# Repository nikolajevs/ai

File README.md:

# GrowBox — контроллер гроубокса

Прошивка ESP32 и собственная плата управления освещением, вентиляцией, поливом и обогревом. Температура и влажность измеряются внешним SHT4x; настройки доступны через веб-интерфейс, расписания используют RTC, журнал сохраняется на microSD.

## Структура репозитория

| Папка | Содержимое |
| --- | --- |
| [softwareEU/](softwareEU/README.md) | Прошивка PCB_EU для ESP32-WROOM-32E-N4, веб-интерфейс и инструкция по сборке |
| [hardware/](hardware/README.md) | Проекты KiCad 10, BOM, модели деталей, корпус и файлы изготовления |
| [parts-catalog/](parts-catalog/README.md) | Локальный каталог цен и остатков четырёх магазинов: поиск, проверка BOM PCB_EU, подбор аналогов |
| [tests/](tests/) | Автоматические тесты веб-интерфейса |
| [vps-docs/](vps-docs/README.md) | Состояние VPS после удаления KiCad и обслуживание прочих сервисов |

## Аппаратная часть

- [PCB_EU](hardware/PCB_EU/README.md) — текущая плата: ESP32-WROOM-32E-N4, вход 24 В, четыре слоя, 100×100 мм, детали только из магазинов ЕС. Прошивка — [softwareEU/](softwareEU/README.md).
- [PCB_V1](hardware/PCB_V1/README.md) — предыдущий проект платы, отдельный от PCB_EU. Прошивка `softwareEU/` его не поддерживает.
- [cheap-version](hardware/cheap-version/README.md) — вариант платы с использованием имеющихся компонентов. Файлы изготовления и состояние проверок описаны в его [FAB.md](hardware/cheap-version/FAB.md).
- [Корпус](hardware/enclosure/README.md) — параметрическая модель для 3D-печати; перед использованием сверяйте её с выбранной версией платы.

## Начало работы

Для прошивки PCB_EU откройте `softwareEU/softwareEU.ino`; зависимости, загрузка веб-интерфейса и проверки описаны в [softwareEU/README.md](softwareEU/README.md).

Для платы PCB_EU откройте `hardware/PCB_EU/PCB_EU.kicad_pro`; распиновка и состояние разработки описаны в [DESIGN.md](hardware/PCB_EU/DESIGN.md).

Правила работы с репозиторием — [AGENTS.md](AGENTS.md).

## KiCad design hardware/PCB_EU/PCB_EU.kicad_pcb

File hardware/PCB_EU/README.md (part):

# GrowBox — новая плата с европейской закупкой

**EU-0.1, состояние на 23.10.2026: все клеммы и разъёмы у краёв платы, радиатор только у LED1 (Q601 без радиатора), вентиляторы на хидерах KF2510-4A, SHT4x на угловом XH2.54-4P-90; все электролиты сверху, снизу детали не выше 8,05 мм; плата разведена полностью (см. «Разводка 21.10.2026» и «Силовой контур LED2 и ключи LED» в [DESIGN.md](DESIGN.md)); силовой контур LED2 проложен вручную, ключи LED — Q501 TK22E10N1 и Q601 CSD19534KCS; добавлен монитор мощности INA226.** Открыть [PCB_EU.kicad_pro](PCB_EU.kicad_pro) в KiCad 10.0.7. Проект содержит схему и [PCB_EU.kicad_pcb](PCB_EU.kicad_pcb): 196 позиций схемы, 113 сверху / 83 снизу, четыре слоя меди; 1451 участок дорожек, 345 переходных, плоскость GND на In1.Cu и заливки GND на F.Cu/B.Cu. Неразведённых соединений нет; физическая сборка и крепление радиатора на купленной детали не подтверждены.

Сохраняются функции PCB_V1: два LED-канала с общей яркостью, два независимых PWM/тахоканала вентиляторов, PTC, помпа, SHT4x, поплавок, RTC с CR2032, microSD, Wi-Fi и существующие функции интерфейса/расписаний. Функциональное основание — `origin/main` `1d6b1eaf1273149b32eb1cf5c91fc69ff6a6ca09`.

**Прошивка PCB_EU находится в [softwareEU/](../../softwareEU/README.md)**: ESP32-WROOM-32E-N4, 4 МБ, RTC MCP7940N и измерение мощности INA226. Команды сборки, тесты и список стендовых проверок приведены в её README; аппаратные испытания предстоят. Прежний бинарник PCB_V1 несовместим: GPIO и RTC отличаются, например прежний GPIO25 помпы теперь управляет LED.

## Файлы

| Файл | Назначение |
|---|---|
| [DESIGN.md](DESIGN.md) | Решения, GPIO, разъёмы, состояния при сбросе и открытые вопросы |
| [BOM_allocated.csv](BOM_allocated.csv) | Закупка с MPN/артикулами, количеством, реальными Ref и ссылками |
| [BOM_allocated.json](BOM_allocated.json) | Тот же состав для автоматической проверки |
| [design.json](design.json) | Полная спецификация выводов, цепей и компонентов |
| [placement.json](placement.json) | Координаты всех 196 позиций, стороны, предварительные резервы и крепление |
| [Размещение сверху](review/PCB_placement_front.png) / [снизу](review/PCB_placement_back.png) | Native KiCad виды PCB с фактической разводкой; снизу зеркально |
| [routing.json](routing.json) / [review/routing.json](review/routing.json) | План силовых соединений LED1 и проверка физической связности меди, включая обе анодные площадки D501; итог разводки и ширины по классам |
| [routing/](routing) | Сессии Freerouting 2.4.1, из которых `tools/route_board.py` воспроизводит разводку |
| [PCB_EU.kicad_dru](PCB_EU.kicad_dru) | Правил DRC нет: прежние сплошные подключения C609 и C510 после переноса электролитов наверх не нужны |
| [footprint_assignments.json](footprint_assignments.json) | Точные механические назначения для 17 MPN, источники и SHA-256 чертежей |
| [procurement_2026-10-20.json](procurement_2026-10-20.json) | Датированный снимок цен/MOQ; не текущая оферта |
| [review/validation.json](review/validation.json) | Версия KiCad, результат проверок, контрольные суммы исходников |
| [review/connectivity.txt](review/connectivity.txt) | 56 проверок соединений и количества покупок |
| [review/footprints.json](review/footprints.json) | Проверки 196 назначений, нумерации площадок, геометрии и загрузки KiCad |
| [review/footprint_drc.json](review/footprint_drc.json) | DRC изолированных библиотечных образцов; не DRC изделия |
| [review/placement.json](review/placement.json) | Сверка PCB/netlist, courtyards, пайка противоположной стороны, RF и механические резервы |
| [review/pcb_drc.json](review/pcb_drc.json) | DRC реального PCB: 0 геометрических / 0 parity / 0 неразведённых |
| [Посадки 1](review/Footprints_mechanical_1.png) / [Посадки 2](review/Footprints_mechanical_2.png) | Отрисовка 12 механических посадок в KiCad, увеличенных отдельно |
| [review/erc.json](review/erc.json) | ERC KiCad; стандартные отключённые категории перечислены в файле |
| [review/netlist.xml](review/netlist.xml) | Netlist, экспортированный самим KiCad |
| [libraries/SOURCES.md](libraries/SOURCES.md) | Источники графики символов и выбранных посадочных мест |

## Закупка

| Поставщик | Детали, НДС включён | Доставка | Сумма |
|---|---:|---:|---:|
| Electrobase | 39,83 € | 2,99 € | 42,82 € |
| Salvats | 35,55 € | 2,88 € | 38,43 € |
| **Всего** | **75,38 €** | **5,87 €** | **81,25 €** |

81 закупочная строка включает минимальные партии, CR2032 и один комплект охлаждения/крепежа/изоляции (после снятия радиатора с Q601 второй комплект убран 23.10.2026). Две строки (KF2510-4A ×2 и XH2.54-4P-90 ×1) добавлены без магазина и цены; DG306 и DG301R куплены по потребности (6 и 1 шт.), запасных нет. Не включены PCB, БП, нагрузки, внешний SHT4x, карта SD, внешняя термозащита PTC, корпус, внешние провода, программатор и инструменты. Заказ не сделан. Ориентир бюджета — около 80 €, жёсткий потолок проверки — 100 €. Разрешённые магазины на 23.10.2026 (список Игоря): Salvats, Electrobase, Semikom, Lemona; в закупке сейчас Electrobase и Salvats. Farnell, Elektrika и Ormix исключены. Нужен БП 24 В не менее 240 Вт / 10 А и внешний термовыключатель PTC.

В схеме пять подтяжек SD CMD/DAT вместо прежней одной: пачек 10k теперь две (+0,11 €). Для трёх затворов AO3422 используются уже оплаченные 1k из пачки вместо отдельных 100R (−0,09 €). Итого изменение к предыдущему подбору: +0,02 €. Фронты PWM вентиляторов с 1k нужно измерить.

21.10.2026 ключи LED IRF540Z (Salvats, 1,70 €) заменены на Toshiba TK22E10N1 (Salvats, 1,38 €, 22 шт. в наличии, цена от 21.10.2026): −0,64 €. Причина — в DESIGN.md, «Ключи LED».

23.10.2026 по решению Игоря заменены три ключа (DESIGN.md, «Ключи LED» и «Q601 без радиатора»). Q601 (LED2): TK22E10N1 → TI CSD19534KCS (Electrobase, 3,09 €, у поставщика 91 шт.; расчётные потери ~0,37 Вт вместо ~0,65 Вт). Q102 и Q703: IRF1010ESPBF → onsemi FDB5800 (Salvats, 2 × 1,98 €, на складе 4 шт.; 6 мОм вместо 12, затвор ±20 В, посадка TO-263-2 та же). TK22E10N1 нужен один (Q501, 1,38 €): второй не покупается. Изменение: IRF 2,42 € → FDB5800 3,96 € (+1,54 €), TK22E10N1 −1,38 €, CSD19534KCS +3,09 €; итого +3,25 €, закупка 82,50 € → 85,75 €. Цены и наличие этих трёх строк проверены 23.10.2026; остальные строки оставлены по снимку 20–21.10.2026, доставка 5,87 € прежняя, посылок по-прежнему две (Electrobase и Salvats).

23.10.2026 по решению Игоря изменены ещё две части закупки. C301/C302 (нагрузка кварца RTC, нужен C0G): Salvats C1206C100J5GAC → KEMET C1206C100J5GACTU у Electrobase (2 × 0,25 € вместо 2 × 0,10 €, у поставщика больше 1000 шт.; карточка Salvats называет Y5V, карточка Electrobase — 10 пФ 50 В C0G ±5 %, TU — суффикс упаковки), +0,30 €. Второй комплект охлаждения убран: RAD-DY-GF/3, TO220-SET и SMICA-TO220-2 по 1 шт. вместо 2 (−1,38 €), после снятия радиатора с Q601 он не нужен. Итого −1,08 €, закупка 85,75 € → 84,67 €; доставка 5,87 € и две посылки прежние. Цена и наличие C1206C100J5GACTU проверены 23.10.2026.

23.10.2026 по решению Игоря («да все 3» на разбор выгрузки цен магазинов от 23.10.2026; сам файл в репозиторий не добавлен) изменены ещё три части закупки. D501/D601: Vishay SS5P10-M3/86A → SS8PH10-M3/86A (Electrobase, 2 × 0,59 € вместо 2 × 1,09 €, у поставщика больше 1000 шт.; тот же корпус TO-277A и та же посадка, 8 А вместо 5 А), −1,00 €. J201: ZL2019-20 (двусторонняя планка на 20 контактов, 0,63 €) → ZL201-10G (Salvats, обычная однорядная планка на 10 контактов, 0,16 €, на складе 41 шт.; режутся 6 контактов, остаются 4), −0,47 €. DG306 покупается 6 шт. вместо 11, DG301R — 1 шт. вместо 2: запасные клеммы не берутся (−1,95 €). Итого −3,42 €, закупка 84,67 € → 81,25 €; доставка 5,87 € и две посылки прежние. Цена и наличие SS8PH10-M3/86A проверены на странице Electrobase 23.10.2026; цена и остаток ZL201-10G взяты из выгрузки, страницы Salvats в тот момент отвечали 429. Сверка посадки и причины — DESIGN.md, «Выходные диоды D501/D601» и «Разъёмы и точные распиновки».

21.10.2026 добавлено измерение мощности платы (DESIGN.md, «Измерение мощности (INA226)»): INA226AIDGSR (Electrobase, 3,94 € за шт.; карточка товара — катушка 2500 шт., наличие и продажа поштучно не подтверждены), шунт из двух 0R01 2512 3 Вт (Salvats, 2 × 0,24 €) и стабилитрон BZV55-C33 (Salvats, 0,13 €). Резистор 1k и конденсатор 100 нФ взяты из уже оплаченных пачек. Итого +4,55 €.

Исправления 21.10.2026: убран TC4427A и его обвязка (−2,53 € и 10 мкФ −0,22 €), добавлена защита от переполюсовки (второй IRF1010ES +1,21 €, 2×5,6k и 10k +0,09 €), R702 заменён на 4,7k 1206 (+0,04 €). C208 1 мкФ взят из уже оплаченной пачки. Итого −1,41 € к прежним 80,00 €.

## Проверки

**Состояние после правок 23.10.2026 (Q601, Q102, Q703, C301/C302, D501/D601 и J201).** Полный `tools/run_checks.py` выполнен 23.10.2026 на KiCad 10.0.7 (версия отчётов) со Shapely 2.0.3 и `pcbnew` из того же пакета: ERC 0, 56 проверок связности, 2198 проверок посадок, 22 991 проверка размещения, DRC со сверкой схемы 0/0/0, разводка полная (1451 дорожка, 345 переходных), скрининг меди 27 сценариев без флагов, JLCPCB 0 FAIL / 3 WARN. Файлы `review/` обновлены этим прогоном, `review/netlist.xml` — экспорт самого KiCad. Поля MPN и Value у D501/D601 и MPN и Design_note у J201 в `PCB_EU.kicad_pcb` исправлены текстом, геометрия платы не менялась. Пересборка платы из исходников (`build_board.py`, `route_power.py`, `route_board.py`, `silkscreen.py`) совпадает с этим `PCB_EU.kicad_pcb`, кроме формата одной строки трёхмерной модели HS1 (правка из PR #86). Физическая примерка, нагрев и поведение преобразователей этими проверками не подтверждены.

Проверено **KiCad CLI 10.0.7**: ERC 0 ошибок/0 предупреждений; 56 проверок, 498 подключённых выводов. Исключений ERC в проекте нет; сохранены четыре стандартные отключённые категории KiCad, перечисленные в `validation.json`.

Для реального PCB: 22 991 проверка размещения; DRC со сверкой схемы — 0 геометрических нарушений, 0 расхождений и **0 неразведённых соединений**. Сборка из `placement.json` и netlist: `build_board.py` + `route_power.py` + `route_board.py` + `silkscreen.py`; результат пересборки описан выше. Отдельно проверены 328 запланированных объектов меди (силовые контуры LED1 и LED2, ручные выводы LM3429, измерение мощности INA226, силовая медь входа, магистрали и питания PTC/LED1 под 1 oz) и 26 физически связанных групп. Проверены обе стороны, нумерация/цепи площадок, THT-маска, courtyards, запас вокруг паек на противоположной стороне, RF и предварительные механические резервы.

Расчётная проверка меди завершена для первого прототипа: добавлены параллельные переходные и путь питания вентиляторов. Наибольший ток переходного 1,55 А в номинале / 1,90 А при изменении сопротивления гильз вдвое; падение +12V до предохранителя вентиляторов около 31 мВ вместо 123 мВ. Подробности, допущения и оставшиеся испытания — DESIGN.md, «Медь и токи»; 27 сценариев — [review/power_copper.json](review/power_copper.json). Выбран и записан в PCB стек JLCPCB JLC04161H-7628: 35 мкм меди снаружи / 15,2 мкм внутри, общая толщина с масками 1,6062 мм. Допуски готовой меди и металлизации нужно подтвердить при расчёте заказа фабрикой.

Радиатор Q501 крепится двумя ножками, запаянными в металлизированные отверстия GND посадки HS1, и винтом М3 к фланцу транзистора через изолирующую прокладку и втулку (решение 22.10.2026, размеры — DESIGN.md, «Радиатор Q501»). Физическая примерка и электрическая изоляция, допустимые токи, нагрев и поведение преобразователей проверяются на прототипе. Визуальный осмотр — за пользователем, производственный ZIP пока не выпускается.

Проверки выполнены на **KiCad 10.0.7**, это целевая версия репозитория. `tools/run_checks.py` проверяет только аппаратную часть PCB_EU; старая PCB_V1 в этот прогон не входит. Прошивка `softwareEU/` собирается и тестируется отдельно по [её инструкции](../../softwareEU/README.md#сборка-и-проверки); работа на реальной плате пока не проверена.

Поле `firmware_build` в [review/validation.json](review/validation.json) говорит, что аппаратные проверки сборку прошивки не выполняют: `softwareEU/` собирается и тестируется отдельно.

Повторить проверки новой схемы с установленным KiCad 10.0.7:

```sh
python3 hardware/PCB_EU/tools/run_checks.py
```

Другую локальную версию разрешать явно, с записью фактической версии в результат:

```sh
python3 hardware/PCB_EU/tools/run_checks.py --kicad-cli /path/to/kicad-cli --allow-other-version
```

Схемы воспроизводятся без сторонних Python-пакетов:

```sh
python3 hardware/PCB_EU/tools/generate.py
```

Специальные посадки воспроизводятся командой `python3 hardware/PCB_EU/tools/generate_footprints.py`. Дополнительный DRC библиотечных образцов: `python3 hardware/PCB_EU/tools/check_footprint_drc.py --kicad-cli /path/to/kicad-cli`; нужен `pcbnew` той же версии в выбранном Python. Этот DRC не проверяет PCB изделия.

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
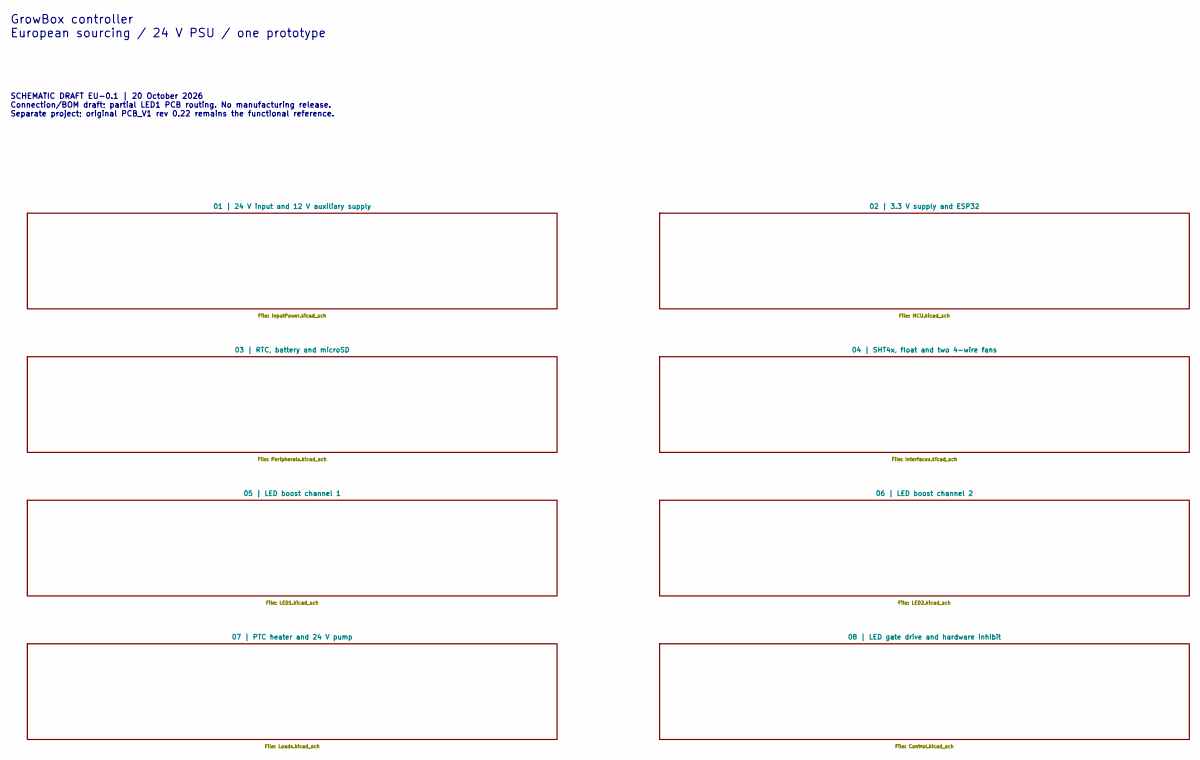
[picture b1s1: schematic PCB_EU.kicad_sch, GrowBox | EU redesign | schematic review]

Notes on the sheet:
GrowBox controller European sourcing / 24 V PSU / one prototype
SCHEMATIC DRAFT EU-0.1 | 20 October 2026 Connection/BOM draft; partial LED1 PCB routing. No manufacturing release. Separate project; original PCB_V1 rev 0.22 remains the functional reference.

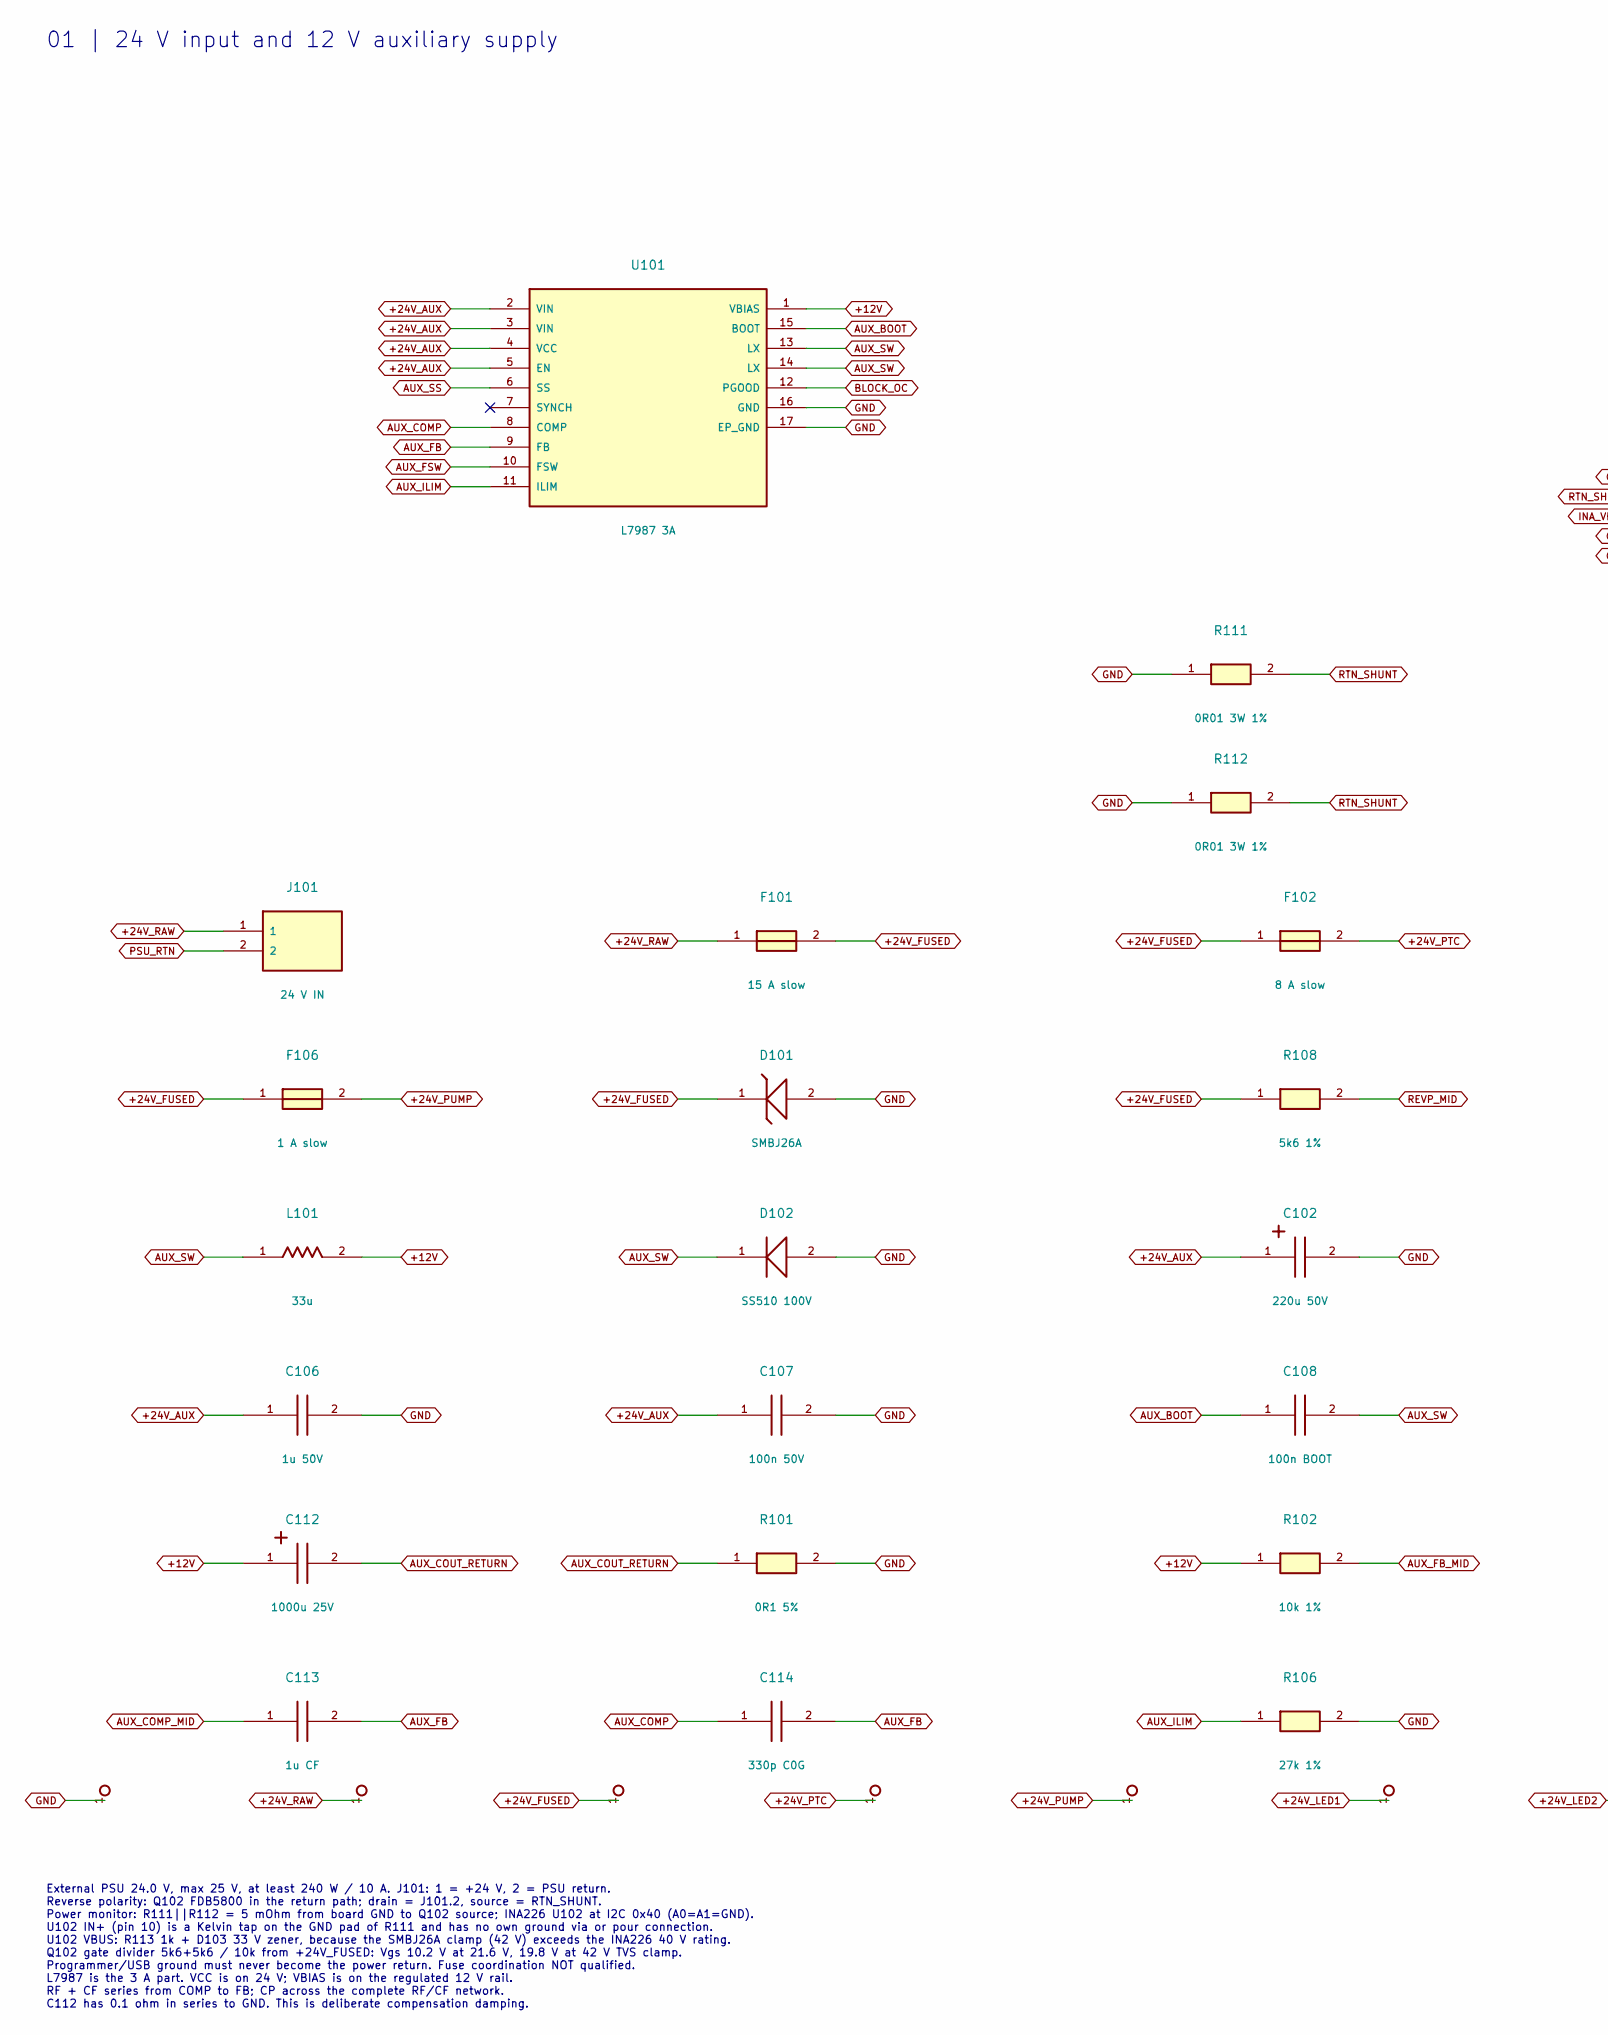
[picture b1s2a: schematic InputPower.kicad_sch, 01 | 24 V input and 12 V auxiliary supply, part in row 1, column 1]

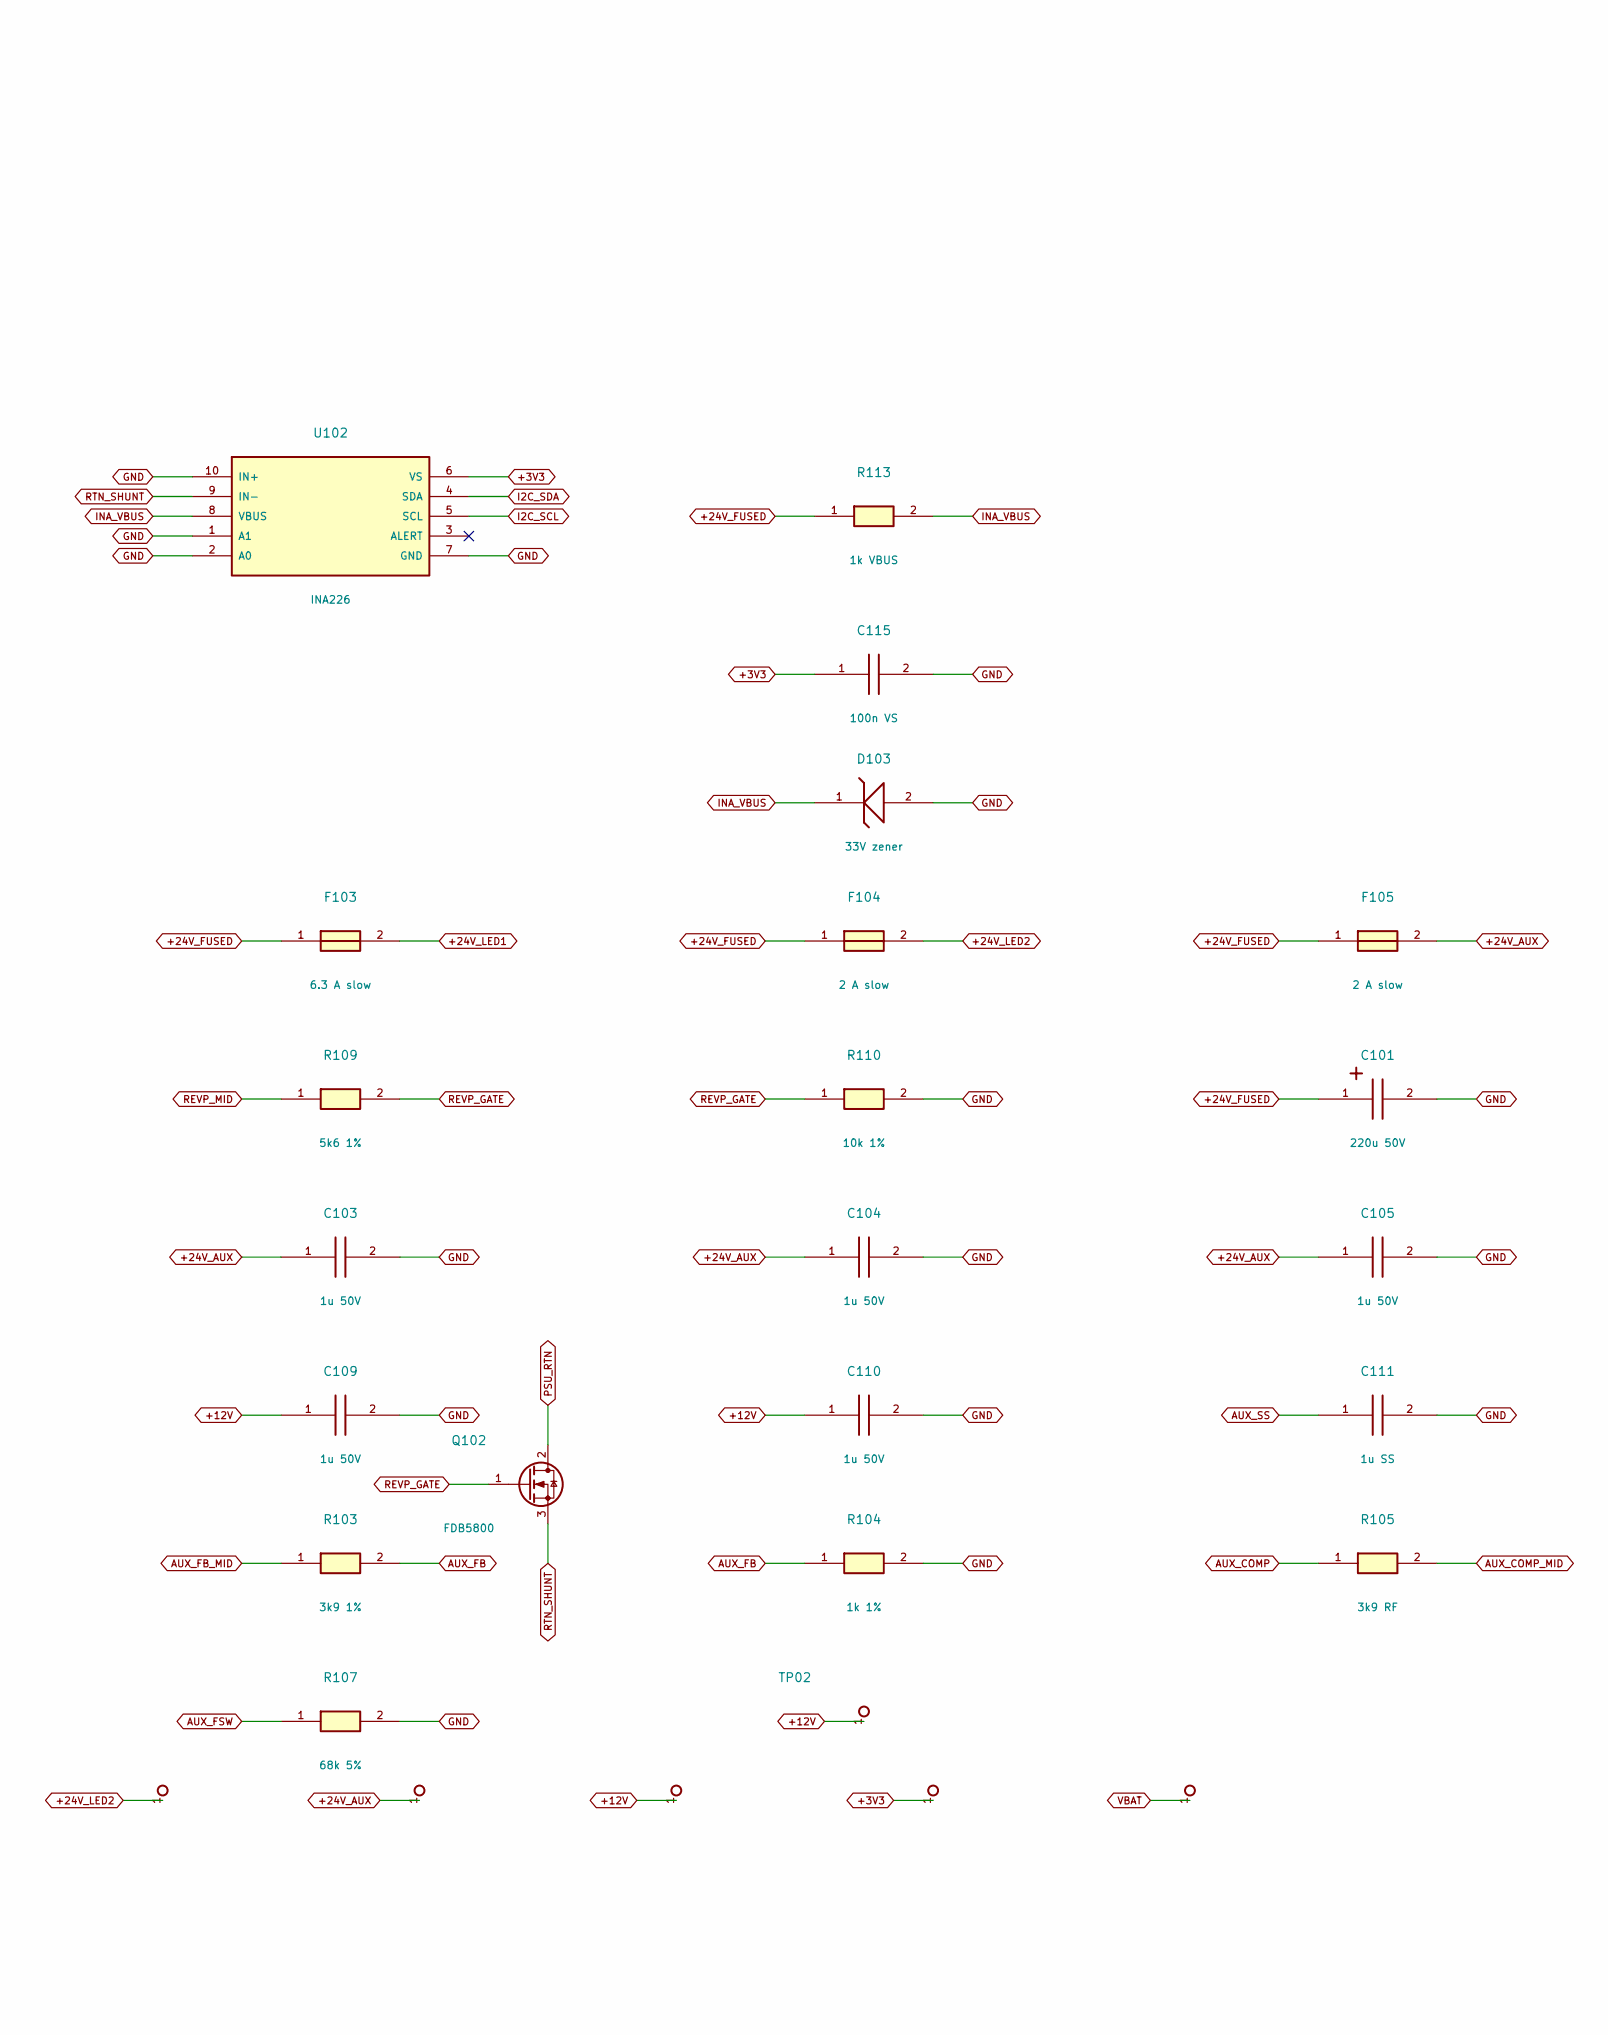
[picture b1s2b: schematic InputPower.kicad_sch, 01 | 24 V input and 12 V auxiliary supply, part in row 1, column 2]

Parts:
C101, C102: 220u 50V; CP_Radial_D10.0mm_P5.00mm; MPN UPW1H221MPD
C103, C104, C105, C106, C109, C110: 1u 50V; C_0805_2012Metric; MPN CL21B105KBFNNNG
C107: 100n 50V; C_0805_2012Metric; MPN CL21B104KBCNNNC
C108: 100n BOOT; C_0805_2012Metric; MPN CL21B104KBCNNNC
C111: 1u SS; C_0805_2012Metric; MPN CL21B105KBFNNNG
C112: 1000u 25V; CP_Radial_D10.0mm_P5.00mm; MPN EEUFR1E102
C113: 1u CF; C_0805_2012Metric; MPN CL21B105KBFNNNG
C114: 330p C0G; C_1206_3216Metric; MPN CC1206JRNPO9331
C115: 100n VS; C_0805_2012Metric; MPN CL21B104KBCNNNC
D101: SMBJ26A; D_SMB; MPN SMBJ26A-E3/52
D102: SS510 100V; D_SMC; MPN SS510-YAN
D103: 33V zener; D_MiniMELF; MPN BZV55-C33
F101: 15 A slow; Fuse_Schurter_UST_USI1206_Reflow; MPN 3413.0330.11
F102: 8 A slow; Fuse_Schurter_UST_USI1206_Reflow; MPN 3413.0327.11
F103: 6.3 A slow; Fuse_Schurter_UST_USI1206_Reflow; MPN 3413.0224.11
F104, F105: 2 A slow; Fuse_Schurter_UMT250; MPN 3403.0169.11
F106: 1 A slow; Fuse_Schurter_UMT250; MPN 3403.0166.11
J101: 24 V IN; TerminalBlock_Degson_DG301R-5.0_1x02; MPN DG301R-5.0-2P12
L101: 33u; L_Jantek_JNRH1207; MPN JNRH1207-330M-A
Q102: FDB5800; TO-263-2; MPN FDB5800
R101: 0R1 5%; R_1206_3216Metric; MPN SMD1206-0R1
R102, R110: 10k 1%; R_1206_3216Metric; MPN SMD1206-10K-1%
R103: 3k9 1%; R_1206_3216Metric; MPN SMD1206-3K9-1%
R104: 1k 1%; R_1206_3216Metric; MPN SMD1206-1K-1%
R105: 3k9 RF; R_1206_3216Metric; MPN SMD1206-3K9-1%
R106: 27k 1%; R_1206_3216Metric; MPN SMD1206-27K-1%
R107: 68k 5%; R_1206_3216Metric; MPN SMD1206-68K
R108, R109: 5k6 1%; R_1206_3216Metric; MPN SMD1206 5K6 1%
R111, R112: 0R01 3W 1%; R_2512_6332Metric; MPN SMD2512-0R01-1%-3W
R113: 1k VBUS; R_0603_1608Metric; MPN SMD0603-1K
TP02: +12V; TestPoint_Pad_D1.0mm
U101: L7987 3A; HTSSOP-16-1EP_4.4x5mm_P0.65mm_EP3x3mm; MPN L7987
U102: INA226; VSSOP-10_3x3mm_P0.5mm; MPN INA226AIDGSR

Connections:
+3V3: C115.1, U102.6 (VS); also elsewhere on the board
+12V: C109.1, C110.1, C112.1, L101.2, R102.1, TP02.1, U101.1 (VBIAS); also elsewhere on the board
+24V_AUX: C102.1, C103.1, C104.1, C105.1, C106.1, C107.1, F105.2, U101.2 (VIN), U101.3 (VIN), U101.4 (VCC), U101.5 (EN)
+24V_FUSED: C101.1, D101.1 (K), F101.2, F102.1, F103.1, F104.1, F105.1, F106.1, R108.1, R113.1; also elsewhere on the board
+24V_LED1: F103.2; also elsewhere on the board
+24V_LED2: F104.2; also elsewhere on the board
+24V_PTC: F102.2; also elsewhere on the board
+24V_PUMP: F106.2; also elsewhere on the board
+24V_RAW: F101.1, J101.1
AUX_BOOT: C108.1, U101.15 (BOOT)
AUX_COMP: C114.1, R105.1, U101.8 (COMP)
AUX_COMP_MID: C113.1, R105.2
AUX_COUT_RETURN: C112.2, R101.1
AUX_FB: C113.2, C114.2, R103.2, R104.1, U101.9 (FB)
AUX_FB_MID: R102.2, R103.1
AUX_FSW: R107.1, U101.10 (FSW)
AUX_ILIM: R106.1, U101.11 (ILIM)
AUX_SS: C111.1, U101.6 (SS)
AUX_SW: C108.2, D102.1 (K), L101.1, U101.13 (LX), U101.14 (LX)
BLOCK_OC: U101.12 (PGOOD); also elsewhere on the board
GND: C101.2, C102.2, C103.2, C104.2, C105.2, C106.2, C107.2, C109.2, C110.2, C111.2, C115.2, D101.2 (A), D102.2 (A), D103.2 (A), R101.2, R104.2, R106.2, R107.2, R110.2, R111.1, R112.1, U101.16 (GND), U101.17 (EP_GND), U102.1 (A1), U102.2 (A0), U102.7 (GND), U102.10 (IN+); also elsewhere on the board
I2C_SCL: U102.5 (SCL); also elsewhere on the board
I2C_SDA: U102.4 (SDA); also elsewhere on the board
INA_VBUS: D103.1 (K), R113.2, U102.8 (VBUS)
PSU_RTN: J101.2, Q102.2 (D)
REVP_GATE: Q102.1 (G), R109.2, R110.1
REVP_MID: R108.2, R109.1
RTN_SHUNT: Q102.3 (S), R111.2, R112.2, U102.9 (IN-)

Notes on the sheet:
01 | 24 V input and 12 V auxiliary supply
External PSU 24.0 V, max 25 V, at least 240 W / 10 A. J101: 1 = +24 V, 2 = PSU return. Reverse polarity: Q102 FDB5800 in the return path; drain = J101.2, source = RTN_SHUNT. Power monitor: R111||R112 = 5 mOhm from board GND to Q102 source; INA226 U102 at I2C 0x40 (A0=A1=GND). U102 IN+ (pin 10) is a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

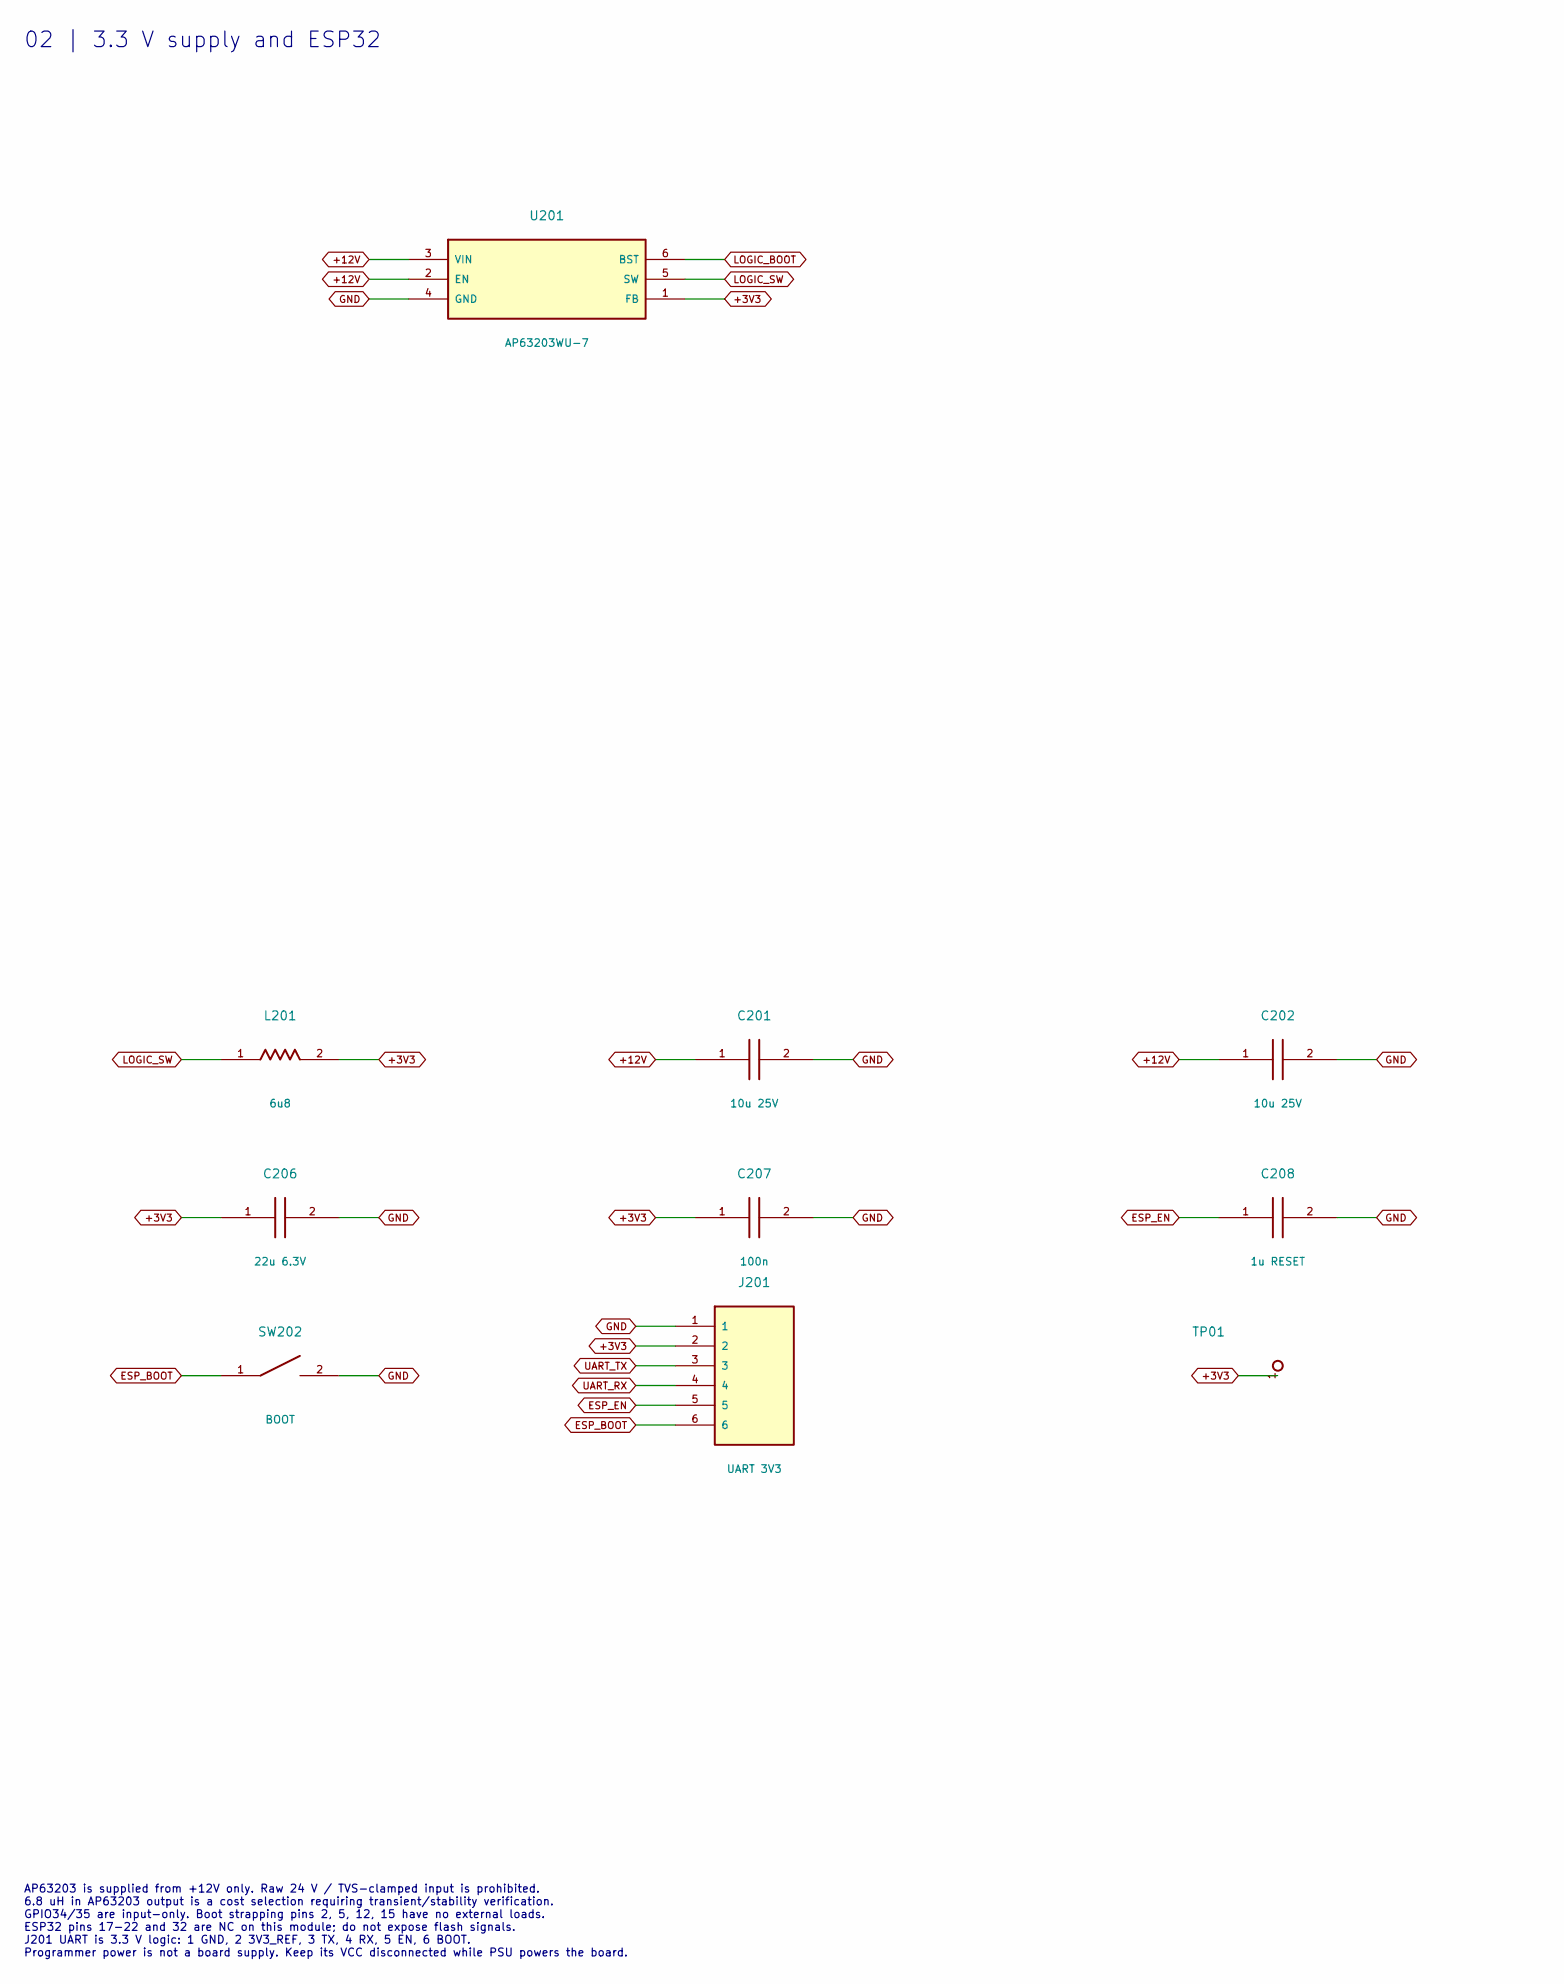
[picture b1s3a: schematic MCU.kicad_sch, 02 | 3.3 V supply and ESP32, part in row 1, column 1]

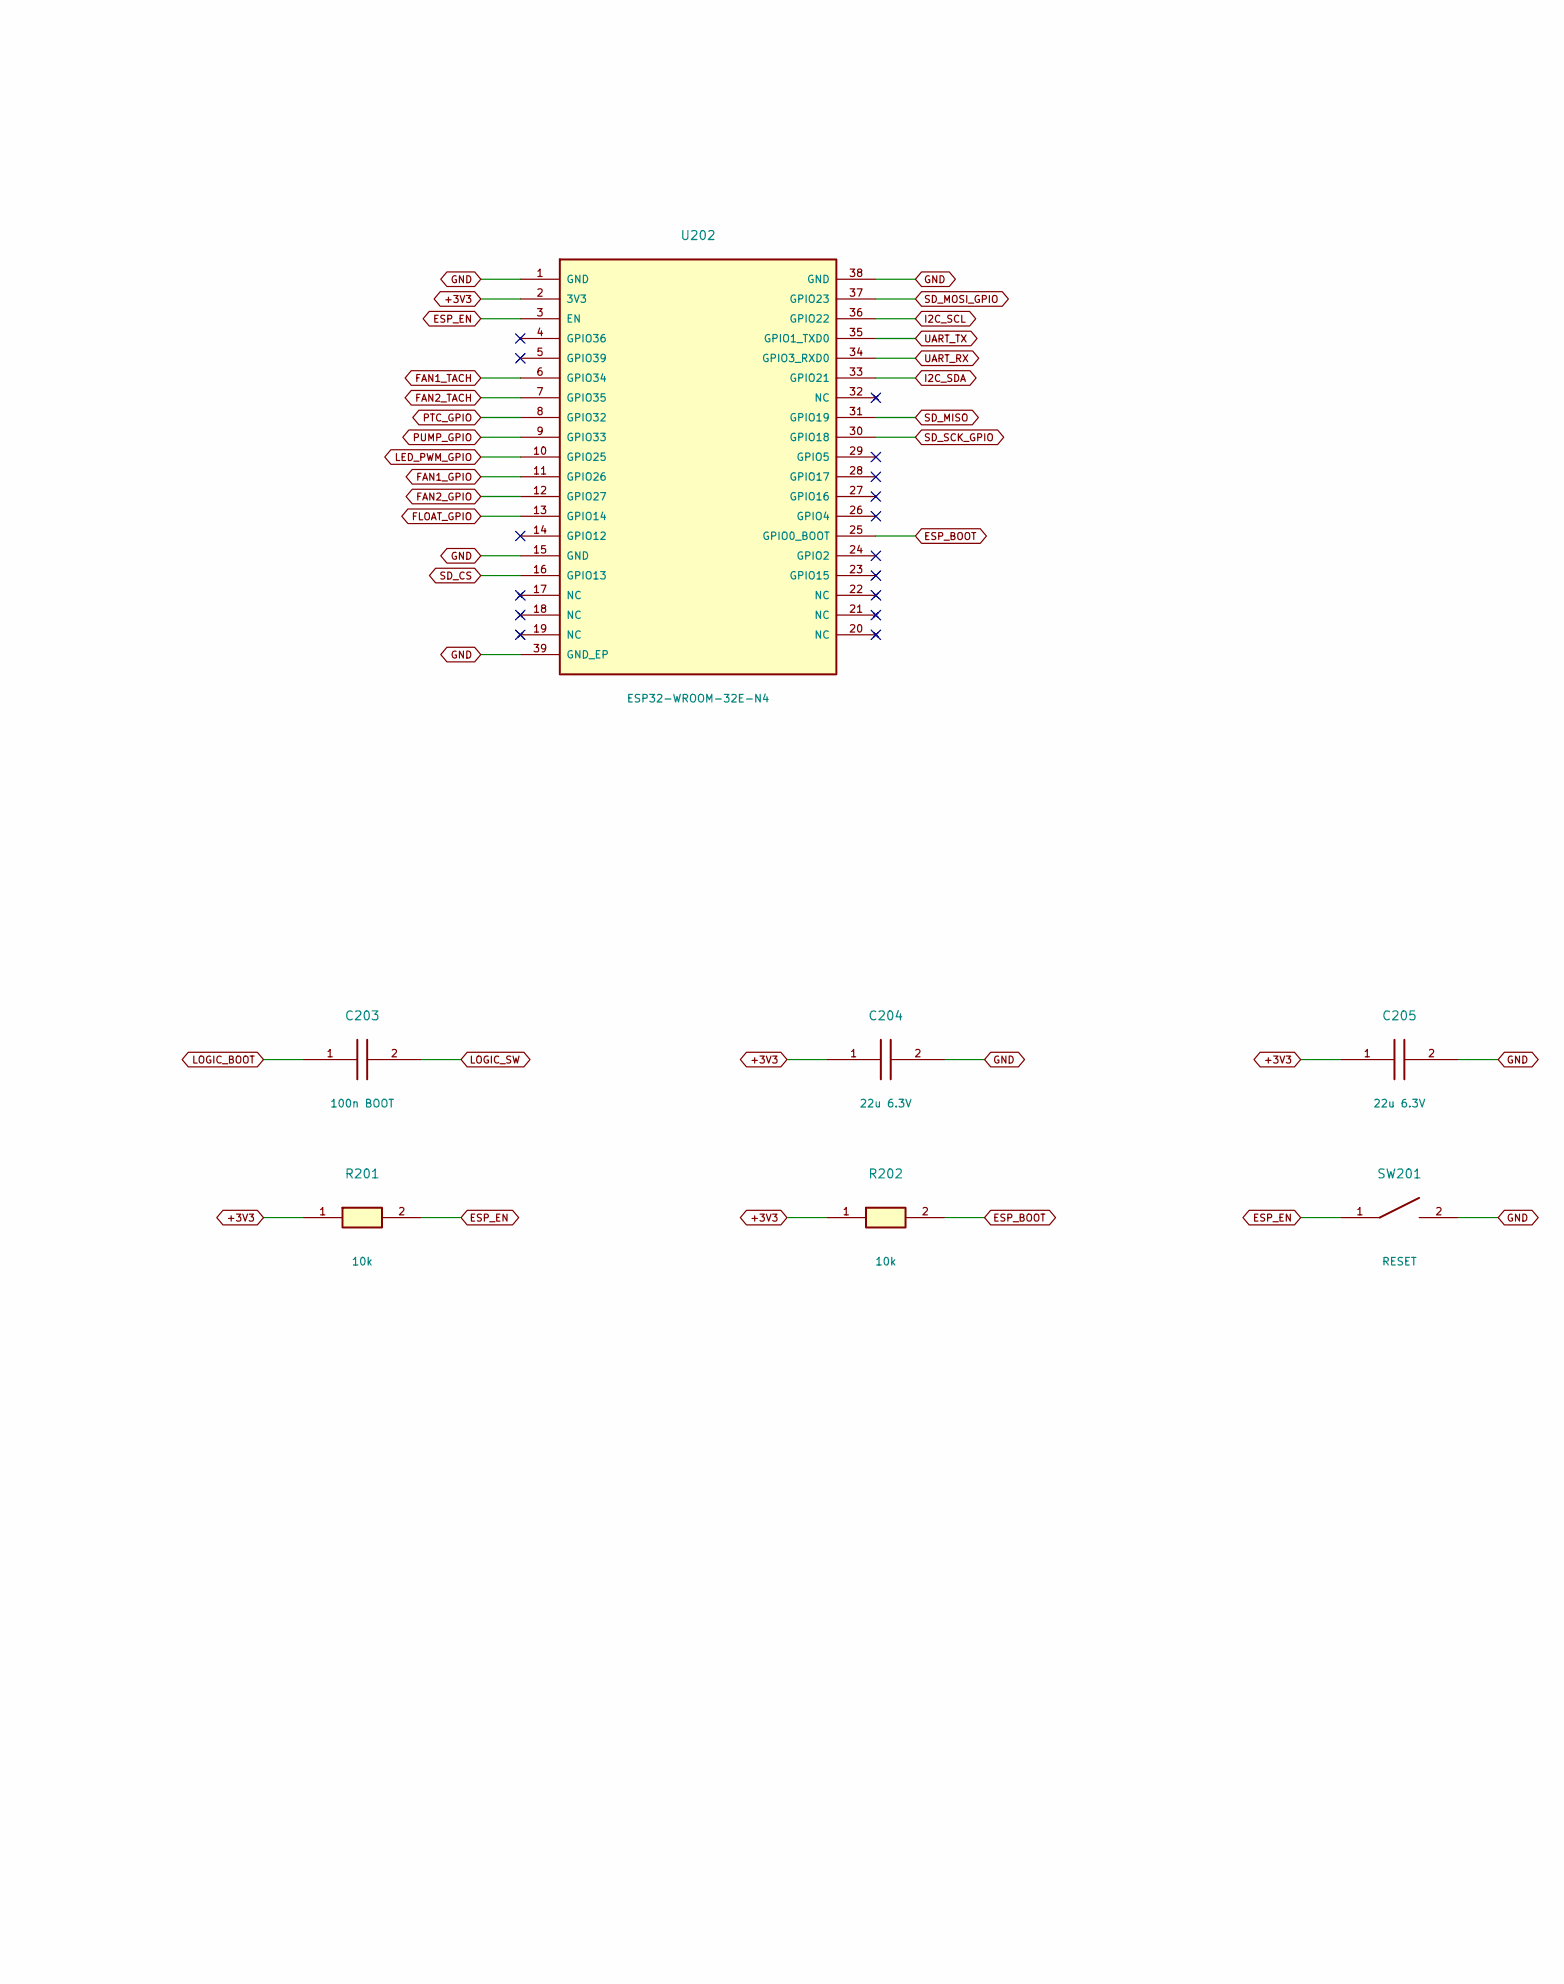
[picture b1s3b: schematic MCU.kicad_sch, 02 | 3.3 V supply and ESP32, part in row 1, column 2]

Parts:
C201, C202: 10u 25V; C_1206_3216Metric; MPN CL31A106KAHNNNE
C203: 100n BOOT; C_0805_2012Metric; MPN CL21B104KBCNNNC
C204, C205, C206: 22u 6.3V; C_1206_3216Metric; MPN CL31A226KQHNNNE
C207: 100n; C_0805_2012Metric; MPN CL21B104KBCNNNC
C208: 1u RESET; C_0805_2012Metric; MPN CL21B105KBFNNNG
J201: UART 3V3; PinHeader_1x06_P2.54mm_Vertical; MPN ZL201-10G
L201: 6u8; L_Bourns_SRN6045; MPN SRN6045-6R8Y
R201, R202: 10k; R_0603_1608Metric; MPN SMD0603-10K
SW201: RESET; SW_Ninigi_TACTB-64K-F; MPN TACTB-64K-F
SW202: BOOT; SW_Ninigi_TACTB-64K-F; MPN TACTB-64K-F
TP01: +3V3; TestPoint_Pad_D1.0mm
U201: AP63203WU-7; TSOT-23-6; MPN AP63203WU-7
U202: ESP32-WROOM-32E-N4; ESP32-WROOM-32E_NoVias; MPN ESP32-WROOM-32E-N4

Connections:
+3V3: C204.1, C205.1, C206.1, C207.1, J201.2, L201.2, R201.1, R202.1, TP01.1, U201.1 (FB), U202.2 (3V3); also elsewhere on the board
+12V: C201.1, C202.1, U201.2 (EN), U201.3 (VIN); also elsewhere on the board
ESP_BOOT: J201.6, R202.2, SW202.1, U202.25 (GPIO0_BOOT)
ESP_EN: C208.1, J201.5, R201.2, SW201.1, U202.3 (EN)
FAN1_GPIO: U202.11 (GPIO26); also elsewhere on the board
FAN1_TACH: U202.6 (GPIO34); also elsewhere on the board
FAN2_GPIO: U202.12 (GPIO27); also elsewhere on the board
FAN2_TACH: U202.7 (GPIO35); also elsewhere on the board
FLOAT_GPIO: U202.13 (GPIO14); also elsewhere on the board
GND: C201.2, C202.2, C204.2, C205.2, C206.2, C207.2, C208.2, J201.1, SW201.2, SW202.2, U201.4 (GND), U202.1 (GND), U202.15 (GND), U202.38 (GND), U202.39 (GND_EP); also elsewhere on the board
I2C_SCL: U202.36 (GPIO22); also elsewhere on the board
I2C_SDA: U202.33 (GPIO21); also elsewhere on the board
LED_PWM_GPIO: U202.10 (GPIO25); also elsewhere on the board
LOGIC_BOOT: C203.1, U201.6 (BST)
LOGIC_SW: C203.2, L201.1, U201.5 (SW)
PTC_GPIO: U202.8 (GPIO32); also elsewhere on the board
PUMP_GPIO: U202.9 (GPIO33); also elsewhere on the board
SD_CS: U202.16 (GPIO13); also elsewhere on the board
SD_MISO: U202.31 (GPIO19); also elsewhere on the board
SD_MOSI_GPIO: U202.37 (GPIO23); also elsewhere on the board
SD_SCK_GPIO: U202.30 (GPIO18); also elsewhere on the board
UART_RX: J201.4, U202.34 (GPIO3_RXD0)
UART_TX: J201.3, U202.35 (GPIO1_TXD0)

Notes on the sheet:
02 | 3.3 V supply and ESP32
AP63203 is supplied from +12V only. Raw 24 V / TVS-clamped input is prohibited. 6.8 uH in AP63203 output is a cost selection requiring transient/stability verification. GPIO34/35 are input-only. Boot strapping pins 2, 5, 12, 15 have no external loads. ESP32 pins 17-22 and 32 are NC on this module; 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
